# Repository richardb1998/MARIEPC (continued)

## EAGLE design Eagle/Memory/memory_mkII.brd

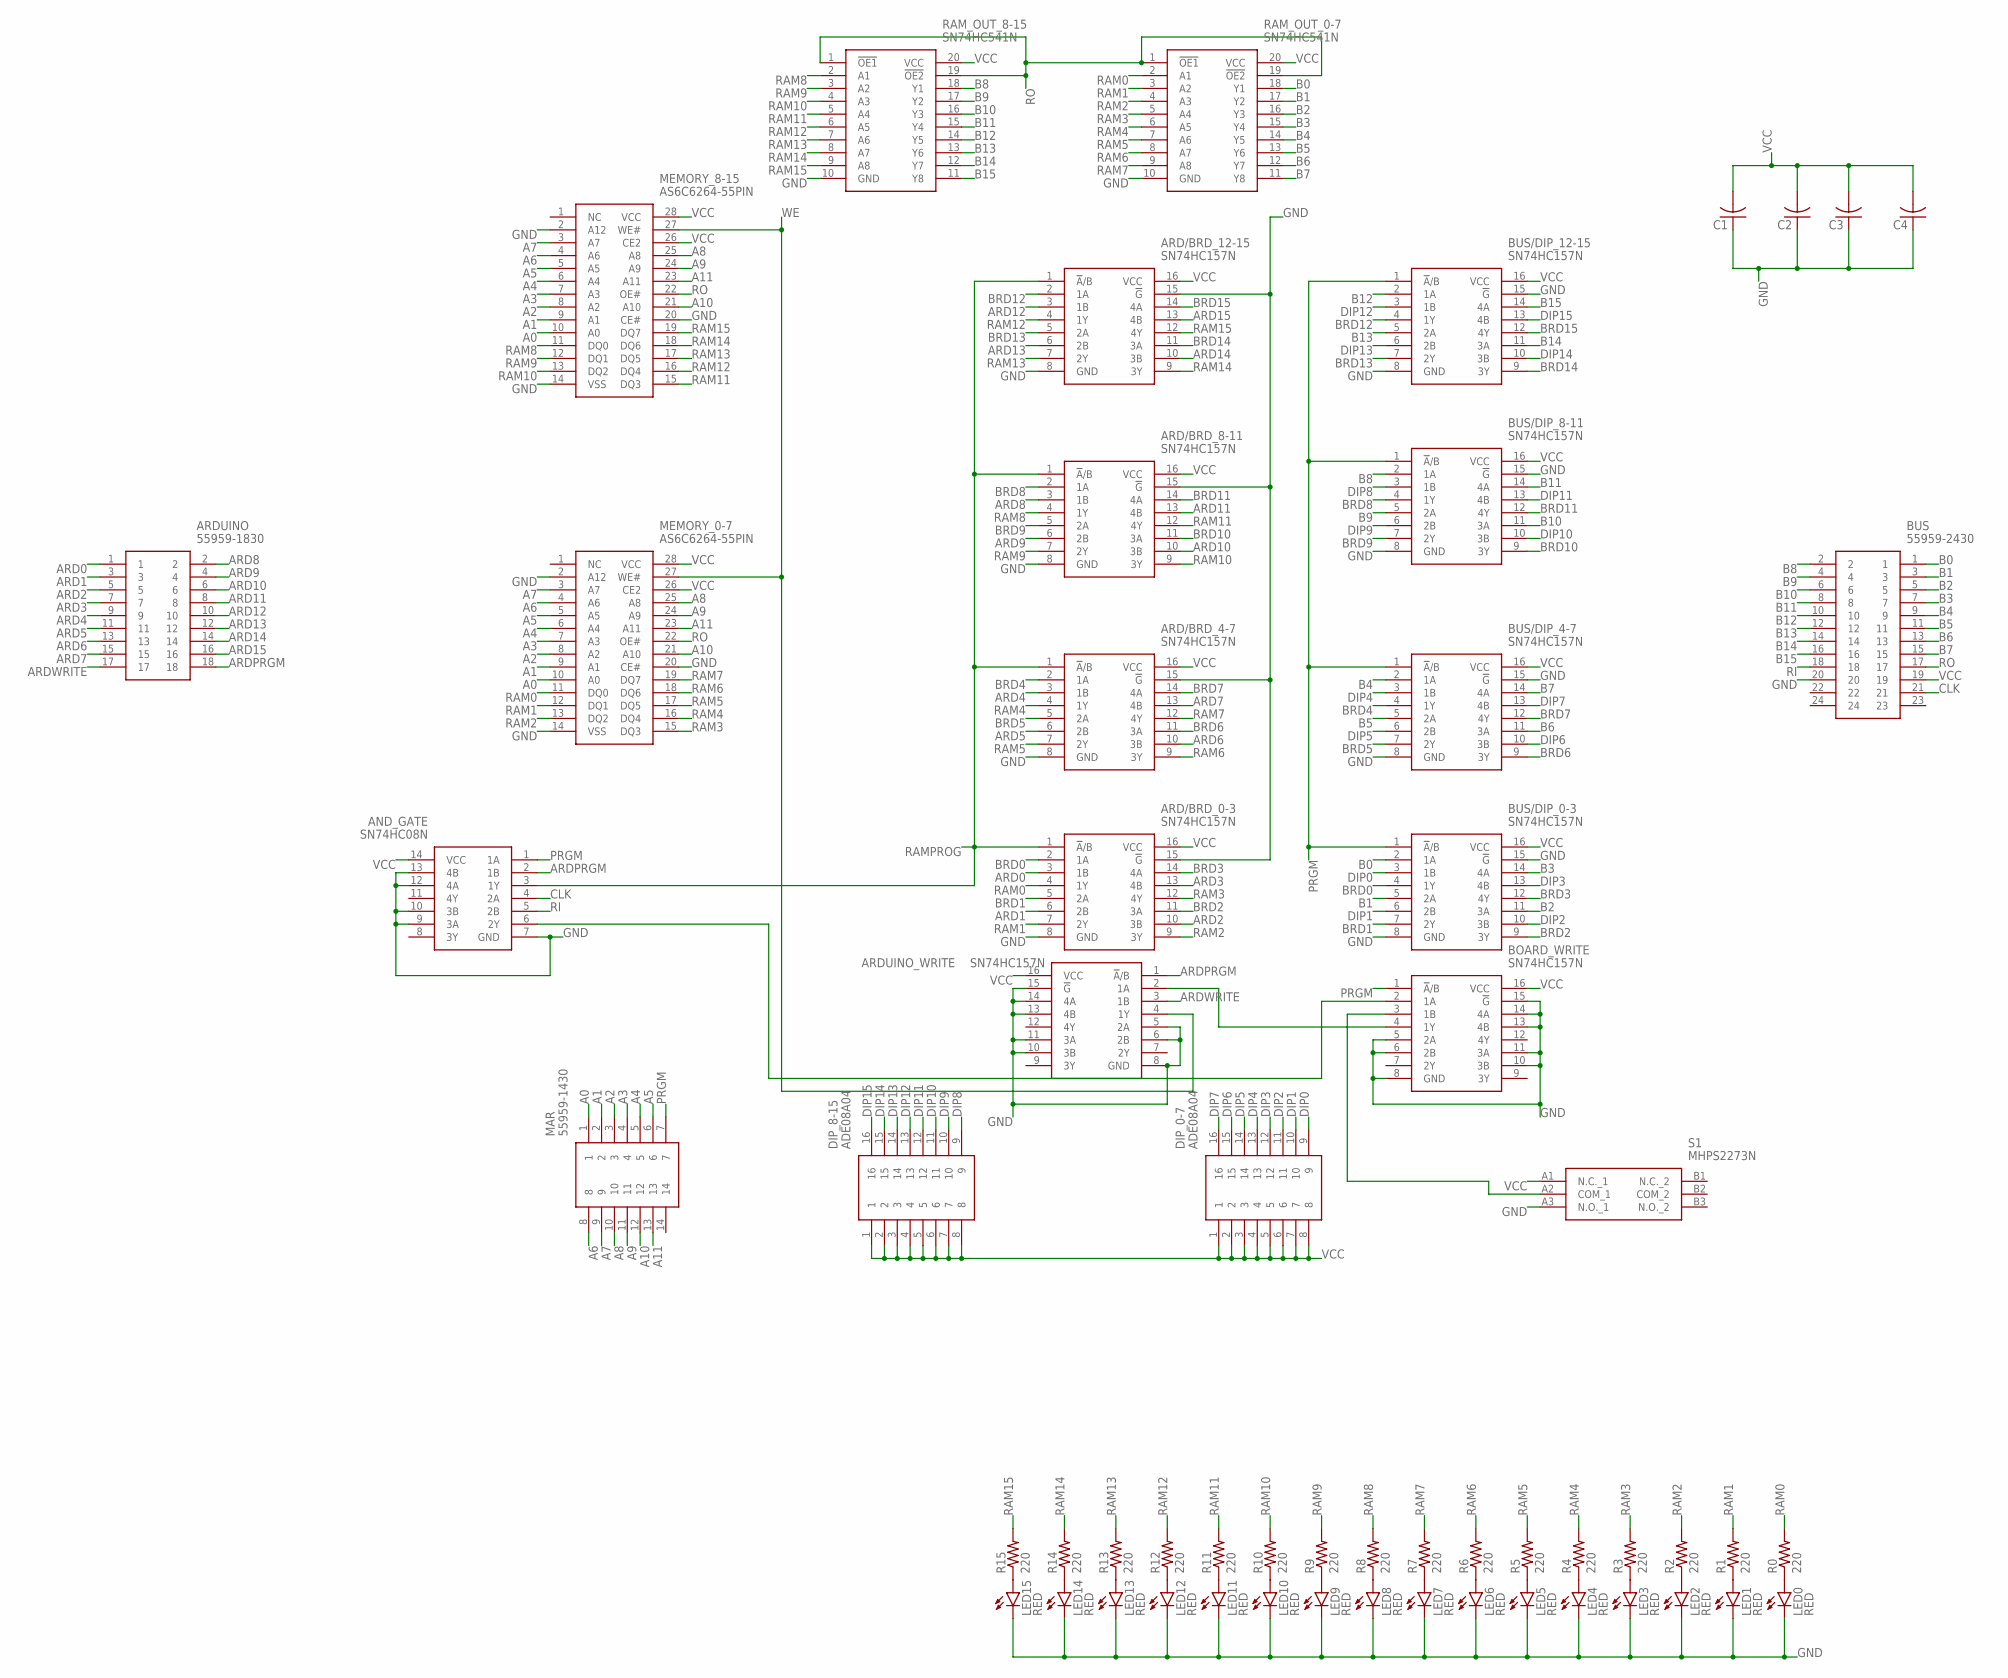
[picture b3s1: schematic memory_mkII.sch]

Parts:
AND_GATE: SN74HC08N; DIP794W53P254L1930H508Q14N
ARD/BRD_0-3, ARD/BRD_4-7, ARD/BRD_8-11, ARD/BRD_12-15: SN74HC157N; DIP794W53P254L1930H508Q16N
ARDUINO: 55959-1830; SHDR18W65P250X200_2X9_2140X140
ARDUINO_WRITE: SN74HC157N; DIP794W53P254L1930H508Q16N
BOARD_WRITE: SN74HC157N; DIP794W53P254L1930H508Q16N
BUS: 55959-2430; 559592430
BUS/DIP_0-3, BUS/DIP_4-7, BUS/DIP_8-11, BUS/DIP_12-15: SN74HC157N; DIP794W53P254L1930H508Q16N
C1, C2, C3, C4: C-US025-024X044; C025-024X044
DIP_0-7, DIP_8-15: ADE08A04; DIP810W60P254L2225H590Q16N
LED0, LED1, LED2, LED3, LED4, LED5, LED6, LED7, LED8, LED9, LED10, LED11, LED12, LED13, LED14, LED15: RED; LED3MM
MAR: 55959-1430; 559591430
MEMORY_0-7, MEMORY_8-15: AS6C6264-55PIN; DIP1524W51P254L3632H394Q28N
R0, R1, R2, R3, R4, R5, R6, R7, R8, R9, R10, R11, R12, R13, R14, R15: 220; 0204/7
RAM_OUT_0-7, RAM_OUT_8-15: SN74HC541N; DIP794W53P254L2540H508Q20N
S1: MHPS2273N

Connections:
A0: MAR.1, MEMORY_0-7.10 (A0), MEMORY_8-15.10 (A0)
A1: MAR.2, MEMORY_0-7.9 (A1), MEMORY_8-15.9 (A1)
A2: MAR.3, MEMORY_0-7.8 (A2), MEMORY_8-15.8 (A2)
A3: MAR.4, MEMORY_0-7.7 (A3), MEMORY_8-15.7 (A3)
A4: MAR.5, MEMORY_0-7.6 (A4), MEMORY_8-15.6 (A4)
A5: MAR.6, MEMORY_0-7.5 (A5), MEMORY_8-15.5 (A5)
A6: MAR.8, MEMORY_0-7.4 (A6), MEMORY_8-15.4 (A6)
A7: MAR.9, MEMORY_0-7.3 (A7), MEMORY_8-15.3 (A7)
A8: MAR.10, MEMORY_0-7.25 (A8), MEMORY_8-15.25 (A8)
A9: MAR.11, MEMORY_0-7.24 (A9), MEMORY_8-15.24 (A9)
A10: MAR.12, MEMORY_0-7.21 (A10), MEMORY_8-15.21 (A10)
A11: MAR.13, MEMORY_0-7.23 (A11), MEMORY_8-15.23 (A11)
ARD0: ARD/BRD_0-3.3 (1B), ARDUINO.1
ARD1: ARD/BRD_0-3.6 (2B), ARDUINO.3
ARD2: ARD/BRD_0-3.10 (3B), ARDUINO.5
ARD3: ARD/BRD_0-3.13 (4B), ARDUINO.7
ARD4: ARD/BRD_4-7.3 (1B), ARDUINO.9
ARD5: ARD/BRD_4-7.6 (2B), ARDUINO.11
ARD6: ARD/BRD_4-7.10 (3B), ARDUINO.13
ARD7: ARD/BRD_4-7.13 (4B), ARDUINO.15
ARD8: ARD/BRD_8-11.3 (1B), ARDUINO.2
ARD9: ARD/BRD_8-11.6 (2B), ARDUINO.4
ARD10: ARD/BRD_8-11.10 (3B), ARDUINO.6
ARD11: ARD/BRD_8-11.13 (4B), ARDUINO.8
ARD12: ARD/BRD_12-15.3 (1B), ARDUINO.10
ARD13: ARD/BRD_12-15.6 (2B), ARDUINO.12
ARD14: ARD/BRD_12-15.10 (3B), ARDUINO.14
ARD15: ARD/BRD_12-15.13 (4B), ARDUINO.16
ARDPRGM: AND_GATE.2 (1B), ARDUINO.18, ARDUINO_WRITE.1 (!A!/B)
ARDWRITE: ARDUINO.17, ARDUINO_WRITE.3 (1B)
B0: BUS.1, BUS/DIP_0-3.2 (1A), RAM_OUT_0-7.18 (Y1)
B1: BUS.3, BUS/DIP_0-3.5 (2A), RAM_OUT_0-7.17 (Y2)
B2: BUS.5, BUS/DIP_0-3.11 (3A), RAM_OUT_0-7.16 (Y3)
B3: BUS.7, BUS/DIP_0-3.14 (4A), RAM_OUT_0-7.15 (Y4)
B4: BUS.9, BUS/DIP_4-7.2 (1A), RAM_OUT_0-7.14 (Y5)
B5: BUS.11, BUS/DIP_4-7.5 (2A), RAM_OUT_0-7.13 (Y6)
B6: BUS.13, BUS/DIP_4-7.11 (3A), RAM_OUT_0-7.12 (Y7)
B7: BUS.15, BUS/DIP_4-7.14 (4A), RAM_OUT_0-7.11 (Y8)
B8: BUS.2, BUS/DIP_8-11.2 (1A), RAM_OUT_8-15.18 (Y1)
B9: BUS.4, BUS/DIP_8-11.5 (2A), RAM_OUT_8-15.17 (Y2)
B10: BUS.6, BUS/DIP_8-11.11 (3A), RAM_OUT_8-15.16 (Y3)
B11: BUS.8, BUS/DIP_8-11.14 (4A), RAM_OUT_8-15.15 (Y4)
B12: BUS.10, BUS/DIP_12-15.2 (1A), RAM_OUT_8-15.14 (Y5)
B13: BUS.12, BUS/DIP_12-15.5 (2A), RAM_OUT_8-15.13 (Y6)
B14: BUS.14, BUS/DIP_12-15.11 (3A), RAM_OUT_8-15.12 (Y7)
B15: BUS.16, BUS/DIP_12-15.14 (4A), RAM_OUT_8-15.11 (Y8)
BRD0: ARD/BRD_0-3.2 (1A), BUS/DIP_0-3.4 (1Y)
BRD1: ARD/BRD_0-3.5 (2A), BUS/DIP_0-3.7 (2Y)
BRD2: ARD/BRD_0-3.11 (3A), BUS/DIP_0-3.9 (3Y)
BRD3: ARD/BRD_0-3.14 (4A), BUS/DIP_0-3.12 (4Y)
BRD4: ARD/BRD_4-7.2 (1A), BUS/DIP_4-7.4 (1Y)
BRD5: ARD/BRD_4-7.5 (2A), BUS/DIP_4-7.7 (2Y)
BRD6: ARD/BRD_4-7.11 (3A), BUS/DIP_4-7.9 (3Y)
BRD7: ARD/BRD_4-7.14 (4A), BUS/DIP_4-7.12 (4Y)
BRD8: ARD/BRD_8-11.2 (1A), BUS/DIP_8-11.4 (1Y)
BRD9: ARD/BRD_8-11.5 (2A), BUS/DIP_8-11.7 (2Y)
BRD10: ARD/BRD_8-11.11 (3A), BUS/DIP_8-11.9 (3Y)
BRD11: ARD/BRD_8-11.14 (4A), BUS/DIP_8-11.12 (4Y)
BRD12: ARD/BRD_12-15.2 (1A), BUS/DIP_12-15.4 (1Y)
BRD13: ARD/BRD_12-15.5 (2A), BUS/DIP_12-15.7 (2Y)
BRD14: ARD/BRD_12-15.11 (3A), BUS/DIP_12-15.9 (3Y)
BRD15: ARD/BRD_12-15.14 (4A), BUS/DIP_12-15.12 (4Y)
CLK: AND_GATE.4 (2A), BUS.21
DIP0: BUS/DIP_0-3.3 (1B), DIP_0-7.9
DIP1: BUS/DIP_0-3.6 (2B), DIP_0-7.10
DIP2: BUS/DIP_0-3.10 (3B), DIP_0-7.11
DIP3: BUS/DIP_0-3.13 (4B), DIP_0-7.12
DIP4: BUS/DIP_4-7.3 (1B), DIP_0-7.13
DIP5: BUS/DIP_4-7.6 (2B), DIP_0-7.14
DIP6: BUS/DIP_4-7.10 (3B), DIP_0-7.15
DIP7: BUS/DIP_4-7.13 (4B), DIP_0-7.16
DIP8: BUS/DIP_8-11.3 (1B), DIP_8-15.9
DIP9: BUS/DIP_8-11.6 (2B), DIP_8-15.10
DIP10: BUS/DIP_8-11.10 (3B), DIP_8-15.11
DIP11: BUS/DIP_8-11.13 (4B), DIP_8-15.12
DIP12: BUS/DIP_12-15.3 (1B), DIP_8-15.13
DIP13: BUS/DIP_12-15.6 (2B), DIP_8-15.14
DIP14: BUS/DIP_12-15.10 (3B), DIP_8-15.15
DIP15: BUS/DIP_12-15.13 (4B), DIP_8-15.16
GND: AND_GATE.7 (GND), AND_GATE.9 (3A), AND_GATE.10 (3B), AND_GATE.12 (4A), AND_GATE.13 (4B), ARD/BRD_0-3.8 (GND), ARD/BRD_0-3.15 (!G), ARD/BRD_4-7.8 (GND), ARD/BRD_4-7.15 (!G), ARD/BRD_8-11.8 (GND), ARD/BRD_8-11.15 (!G), ARD/BRD_12-15.8 (GND), ARD/BRD_12-15.15 (!G), ARDUINO_WRITE.5 (2A), ARDUINO_WRITE.6 (2B), ARDUINO_WRITE.8 (GND), ARDUINO_WRITE.10 (3B), ARDUINO_WRITE.11 (3A), ARDUINO_WRITE.13 (4B), ARDUINO_WRITE.14 (4A), ARDUINO_WRITE.15 (!G), BOARD_WRITE.5 (2A), BOARD_WRITE.6 (2B), BOARD_WRITE.8 (GND), BOARD_WRITE.10 (3B), BOARD_WRITE.11 (3A), BOARD_WRITE.13 (4B), BOARD_WRITE.14 (4A), BOARD_WRITE.15 (!G), BUS.20, BUS/DIP_0-3.8 (GND), BUS/DIP_0-3.15 (!G), BUS/DIP_4-7.8 (GND), BUS/DIP_4-7.15 (!G), BUS/DIP_8-11.8 (GND), BUS/DIP_8-11.15 (!G), BUS/DIP_12-15.8 (GND), BUS/DIP_12-15.15 (!G), C1.1, C2.1, C3.1, C4.1, LED0.K (C), LED1.K (C), LED2.K (C), LED3.K (C), LED4.K (C), LED5.K (C), LED6.K (C), LED7.K (C), LED8.K (C), LED9.K (C), LED10.K (C), LED11.K (C), LED12.K (C), LED13.K (C), LED14.K (C), LED15.K (C), MEMORY_0-7.2 (A12), MEMORY_0-7.14 (VSS), MEMORY_0-7.20 (CE#), MEMORY_8-15.2 (A12), MEMORY_8-15.14 (VSS), MEMORY_8-15.20 (CE#), RAM_OUT_0-7.10 (GND), RAM_OUT_8-15.10 (GND), S1.A3 (N.O._1)
unnamed: LED1.A, R1.1
unnamed: BOARD_WRITE.3 (1B), S1.A2 (COM_1)
unnamed: ARDUINO_WRITE.2 (1A), BOARD_WRITE.4 (1Y)
unnamed: LED2.A, R2.1
unnamed: LED3.A, R3.1
unnamed: LED4.A, R4.1
unnamed: LED5.A, R5.1
unnamed: LED6.A, R6.1
unnamed: LED7.A, R7.1
unnamed: LED8.A, R8.1
unnamed: LED9.A, R9.1
unnamed: LED10.A, R10.1
unnamed: LED11.A, R11.1
unnamed: LED12.A, R12.1
unnamed: LED13.A, R13.1
unnamed: LED14.A, R14.1
unnamed: LED15.A, R15.1
unnamed: LED0.A, R0.1
PRGM: AND_GATE.1 (1A), BOARD_WRITE.1 (!A!/B), BUS/DIP_0-3.1 (!A!/B), BUS/DIP_4-7.1 (!A!/B), BUS/DIP_8-11.1 (!A!/B), BUS/DIP_12-15.1 (!A!/B), MAR.7
RAM0: ARD/BRD_0-3.4 (1Y), MEMORY_0-7.11 (DQ0), R0.2, RAM_OUT_0-7.2 (A1)
RAM1: ARD/BRD_0-3.7 (2Y), MEMORY_0-7.12 (DQ1), R1.2, RAM_OUT_0-7.3 (A2)
RAM2: ARD/BRD_0-3.9 (3Y), MEMORY_0-7.13 (DQ2), R2.2, RAM_OUT_0-7.4 (A3)
RAM3: ARD/BRD_0-3.12 (4Y), MEMORY_0-7.15 (DQ3), R3.2, RAM_OUT_0-7.5 (A4)
RAM4: ARD/BRD_4-7.4 (1Y), MEMORY_0-7.16 (DQ4), R4.2, RAM_OUT_0-7.6 (A5)
RAM5: ARD/BRD_4-7.7 (2Y), MEMORY_0-7.17 (DQ5), R5.2, RAM_OUT_0-7.7 (A6)
RAM6: ARD/BRD_4-7.9 (3Y), MEMORY_0-7.18 (DQ6), R6.2, RAM_OUT_0-7.8 (A7)
RAM7: ARD/BRD_4-7.12 (4Y), MEMORY_0-7.19 (DQ7), R7.2, RAM_OUT_0-7.9 (A8)
RAM8: ARD/BRD_8-11.4 (1Y), MEMORY_8-15.11 (DQ0), R8.2, RAM_OUT_8-15.2 (A1)
RAM9: ARD/BRD_8-11.7 (2Y), MEMORY_8-15.12 (DQ1), R9.2, RAM_OUT_8-15.3 (A2)
RAM10: ARD/BRD_8-11.9 (3Y), MEMORY_8-15.13 (DQ2), R10.2, RAM_OUT_8-15.4 (A3)
RAM11: ARD/BRD_8-11.12 (4Y), MEMORY_8-15.15 (DQ3), R11.2, RAM_OUT_8-15.5 (A4)
RAM12: ARD/BRD_12-15.4 (1Y), MEMORY_8-15.16 (DQ4), R12.2, RAM_OUT_8-15.6 (A5)
RAM13: ARD/BRD_12-15.7 (2Y), MEMORY_8-15.17 (DQ5), R13.2, RAM_OUT_8-15.7 (A6)
RAM14: ARD/BRD_12-15.9 (3Y), MEMORY_8-15.18 (DQ6), R14.2, RAM_OUT_8-15.8 (A7)
RAM15: ARD/BRD_12-15.12 (4Y), MEMORY_8-15.19 (DQ7), R15.2, RAM_OUT_8-15.9 (A8)
RAMCLK: AND_GATE.6 (2Y), BOARD_WRITE.2 (1A)
RAMPROG: AND_GATE.3 (1Y), ARD/BRD_0-3.1 (!A!/B), ARD/BRD_4-7.1 (!A!/B), ARD/BRD_8-11.1 (!A!/B), ARD/BRD_12-15.1 (!A!/B)
RI: AND_GATE.5 (2B), BUS.18
RO: BUS.17, MEMORY_0-7.22 (OE#), MEMORY_8-15.22 (OE#), RAM_OUT_0-7.1 (!OE1), RAM_OUT_0-7.19 (!OE2), RAM_OUT_8-15.1 (!OE1), RAM_OUT_8-15.19 (!OE2)
VCC: AND_GATE.14 (VCC), ARD/BRD_0-3.16 (VCC), ARD/BRD_4-7.16 (VCC), ARD/BRD_8-11.16 (VCC), ARD/BRD_12-15.16 (VCC), ARDUINO_WRITE.16 (VCC), BOARD_WRITE.16 (VCC), BUS.19, BUS/DIP_0-3.16 (VCC), BUS/DIP_4-7.16 (VCC), BUS/DIP_8-11.16 (VCC), BUS/DIP_12-15.16 (VCC), C1.2, C2.2, C3.2, C4.2, DIP_0-7.1, DIP_0-7.2, DIP_0-7.3, DIP_0-7.4, DIP_0-7.5, DIP_0-7.6, DIP_0-7.7, DIP_0-7.8, DIP_8-15.1, DIP_8-15.2, DIP_8-15.3, DIP_8-15.4, DIP_8-15.5, DIP_8-15.6, DIP_8-15.7, DIP_8-15.8, MEMORY_0-7.26 (CE2), MEMORY_0-7.28 (VCC), MEMORY_8-15.26 (CE2), MEMORY_8-15.28 (VCC), RAM_OUT_0-7.20 (VCC), RAM_OUT_8-15.20 (VCC), S1.A1 (N.C._1)
WE: ARDUINO_WRITE.4 (1Y), MEMORY_0-7.27 (WE#), MEMORY_8-15.27 (WE#)

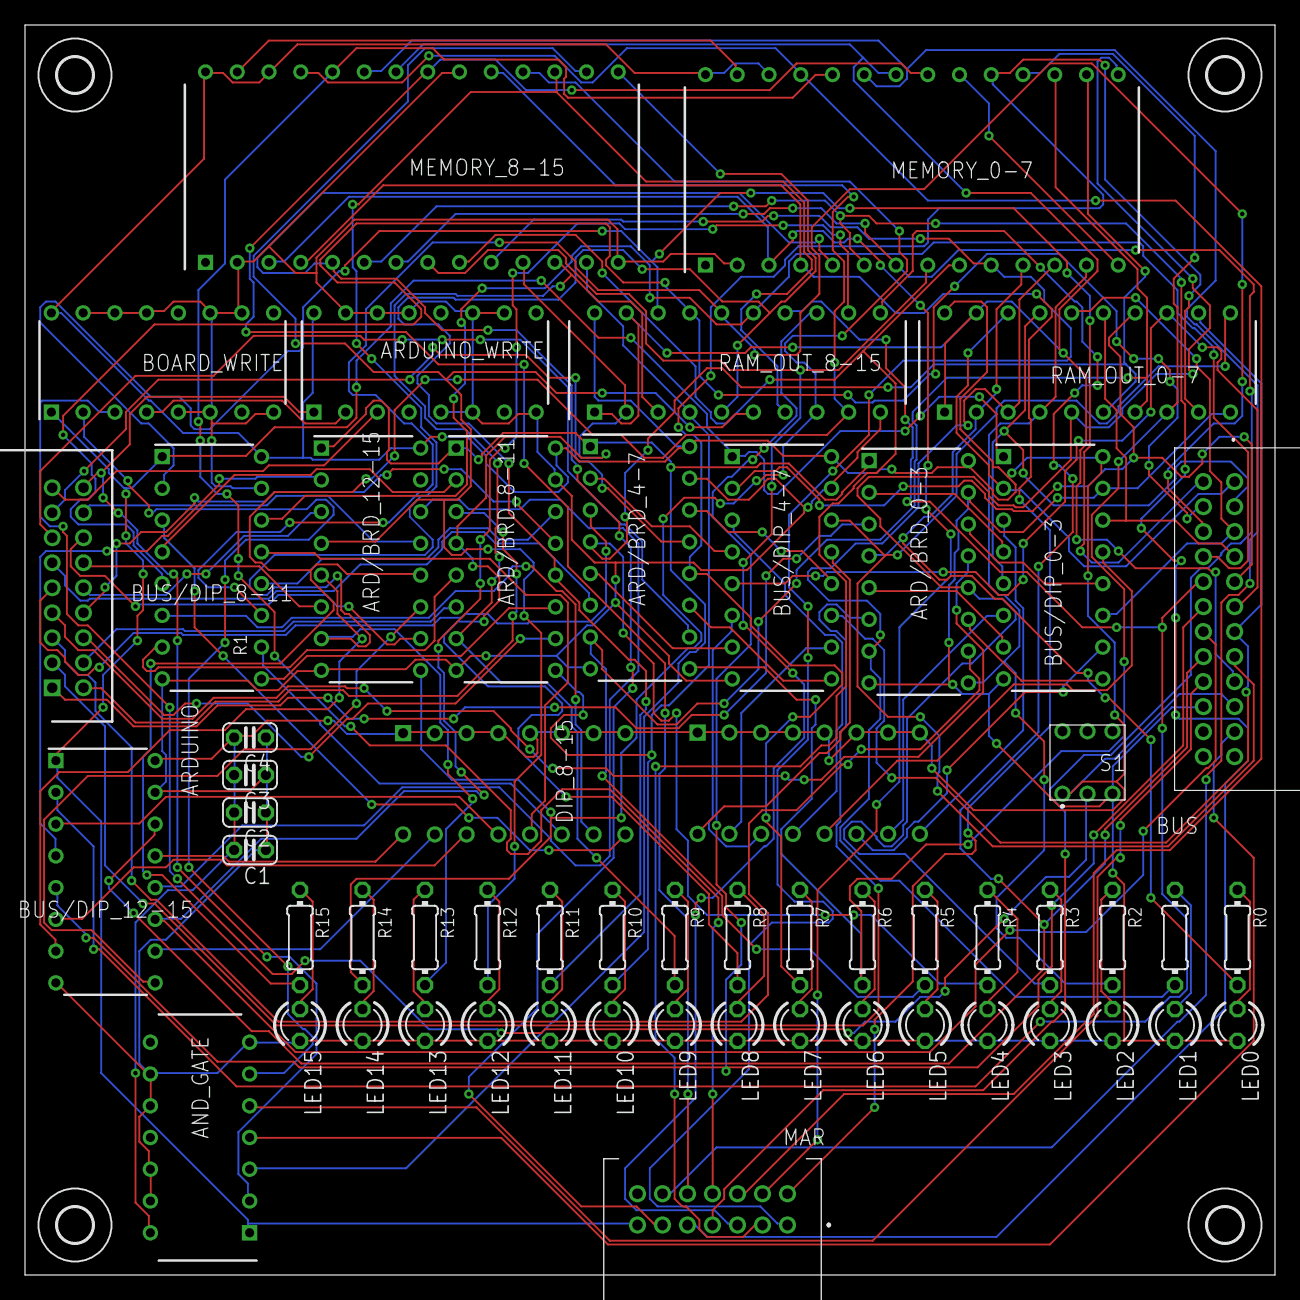
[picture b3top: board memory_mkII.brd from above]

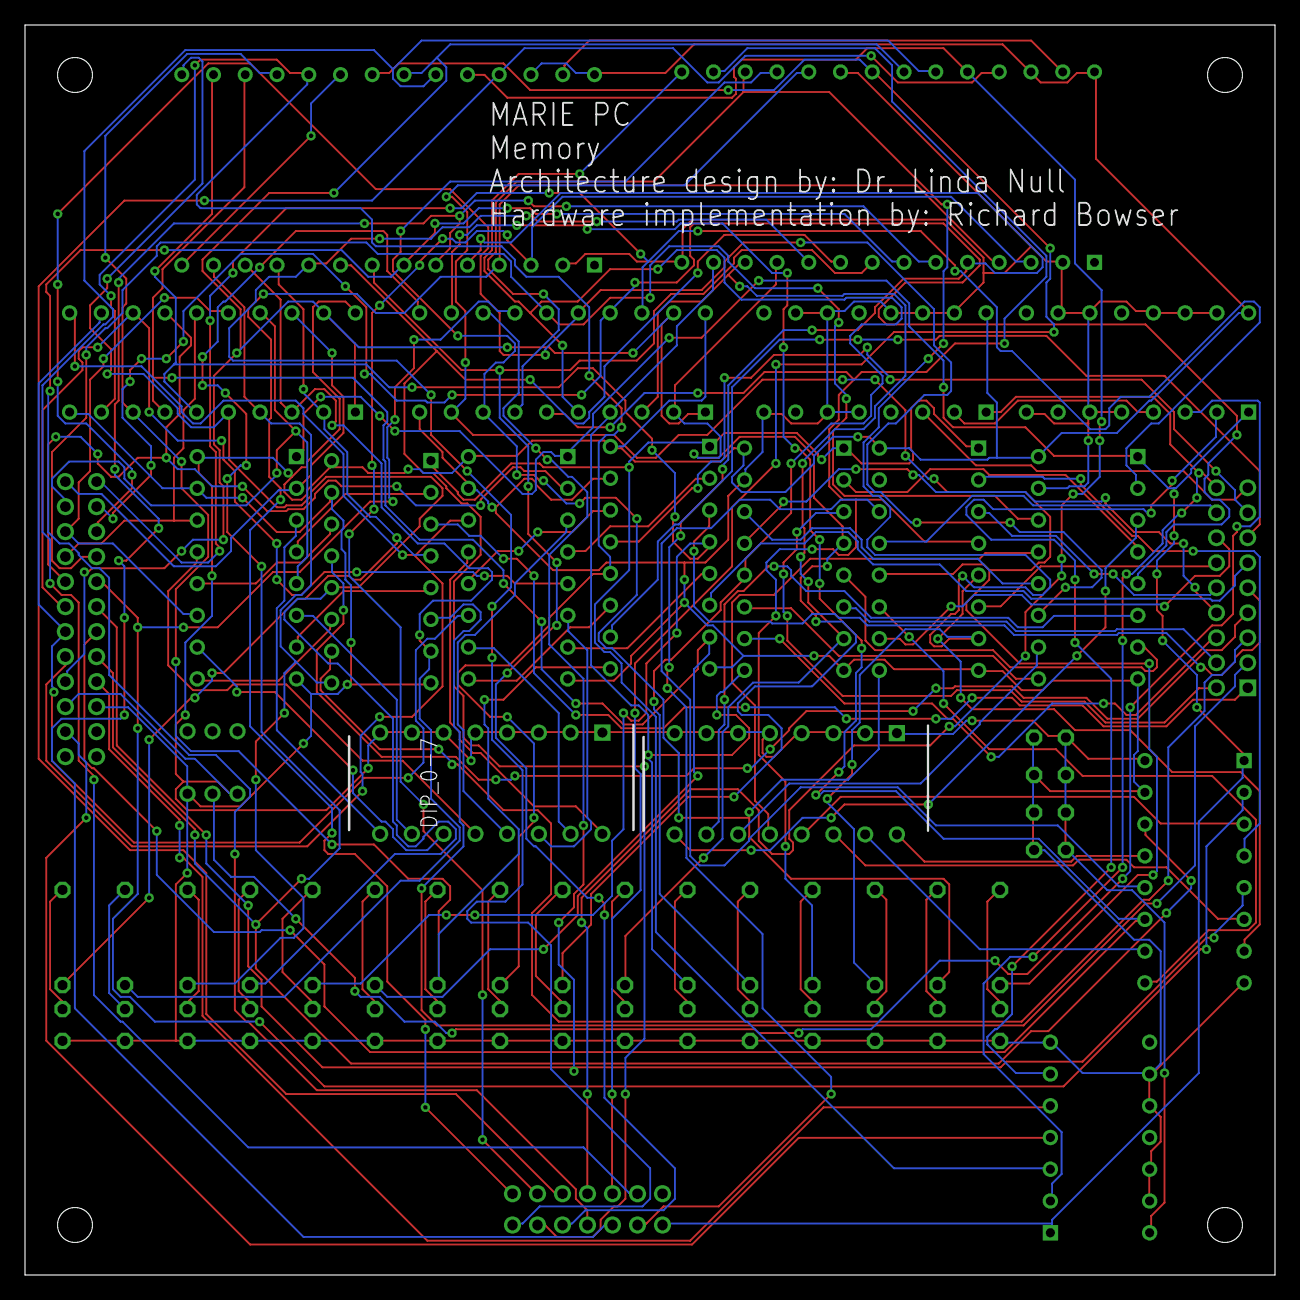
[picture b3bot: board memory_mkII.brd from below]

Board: 2 copper layers, 100.0 x 100.0 mm, 61 parts (2 on the bottom side), 121 nets.

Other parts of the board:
U$1, U$2, U$3, U$4: 2,8

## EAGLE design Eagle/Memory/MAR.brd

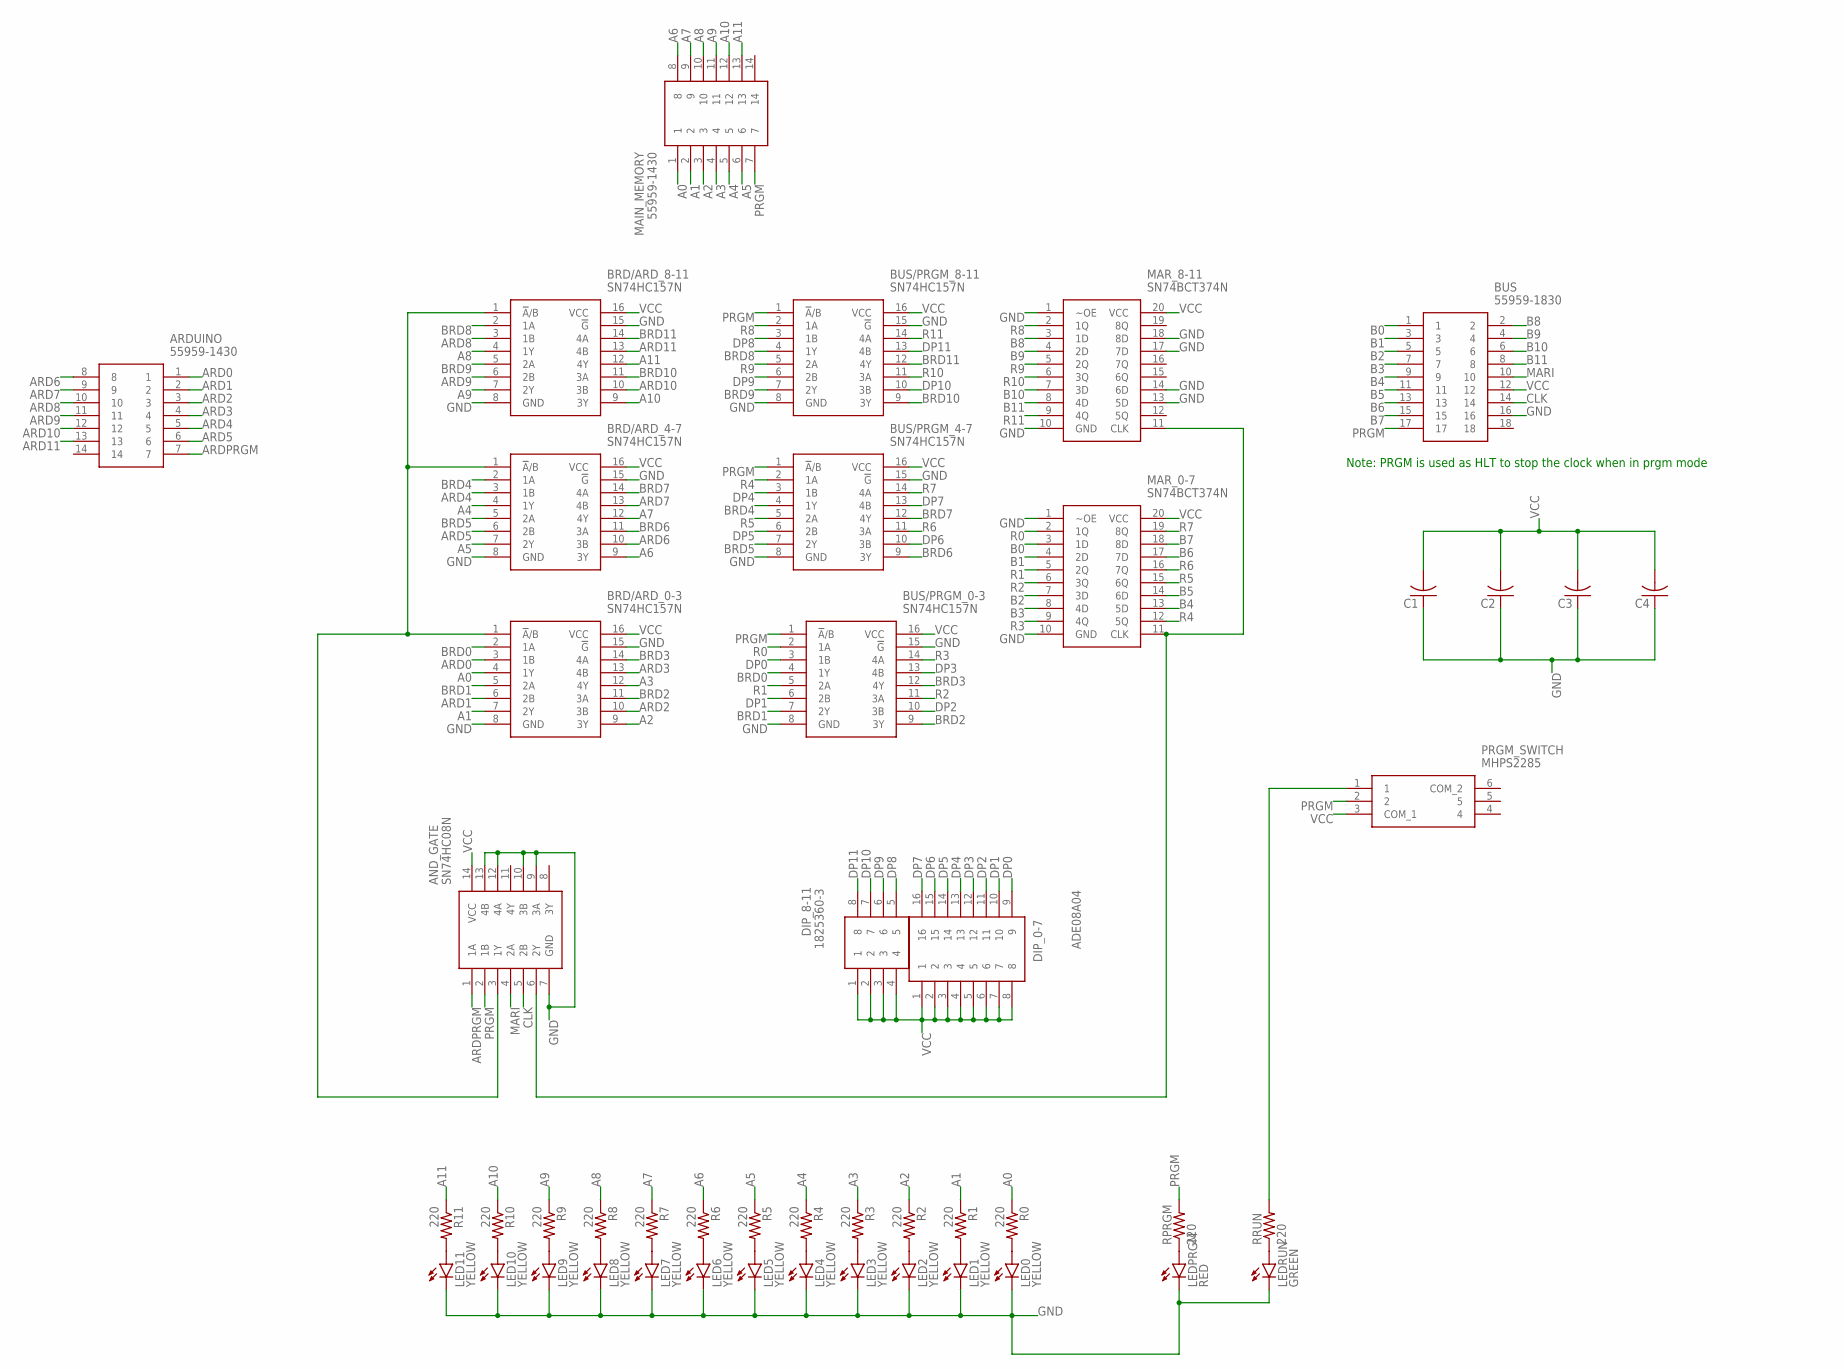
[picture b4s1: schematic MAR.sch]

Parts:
AND_GATE: SN74HC08N; DIP794W53P254L1930H508Q14N
ARDUINO: 55959-1430; 559591430
BRD/ARD_0-3, BRD/ARD_4-7, BRD/ARD_8-11: SN74HC157N; DIP794W53P254L1930H508Q16N
BUS: 55959-1830; SHDR18W65P250X200_2X9_2140X140
BUS/PRGM_0-3, BUS/PRGM_4-7, BUS/PRGM_8-11: SN74HC157N; DIP794W53P254L1930H508Q16N
C1, C2, C3, C4: C-US025-024X044; C025-024X044
DIP_0-7: ADE08A04; DIP810W60P254L2225H590Q16N
DIP_8-11: 1825360-3; DIP813W61P254L1209H351Q8N
LED0, LED1, LED2, LED3, LED4, LED5, LED6, LED7, LED8, LED9, LED10, LED11: YELLOW; LED3MM
LEDPRGM: RED; LED3MM
LEDRUN: GREEN; LED3MM
MAIN_MEMORY: 55959-1430; 559591430
MAR_0-7, MAR_8-11: SN74BCT374N; DIP254P762X508-20
PRGM_SWITCH: MHPS2285
R0, R1, R2, R3, R4, R5, R6, R7, R8, R9, R10, R11: 220; 0204/7
RPRGM: 220; 0204/7
RRUN: 220; 0204/7

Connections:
A0: BRD/ARD_0-3.4 (1Y), MAIN_MEMORY.1, R0.1
A1: BRD/ARD_0-3.7 (2Y), MAIN_MEMORY.2, R1.1
A2: BRD/ARD_0-3.9 (3Y), MAIN_MEMORY.3, R2.1
A3: BRD/ARD_0-3.12 (4Y), MAIN_MEMORY.4, R3.1
A4: BRD/ARD_4-7.4 (1Y), MAIN_MEMORY.5, R4.1
A5: BRD/ARD_4-7.7 (2Y), MAIN_MEMORY.6, R5.1
A6: BRD/ARD_4-7.9 (3Y), MAIN_MEMORY.8, R6.1
A7: BRD/ARD_4-7.12 (4Y), MAIN_MEMORY.9, R7.1
A8: BRD/ARD_8-11.4 (1Y), MAIN_MEMORY.10, R8.1
A9: BRD/ARD_8-11.7 (2Y), MAIN_MEMORY.11, R9.1
A10: BRD/ARD_8-11.9 (3Y), MAIN_MEMORY.12, R10.1
A11: BRD/ARD_8-11.12 (4Y), MAIN_MEMORY.13, R11.1
ARD0: ARDUINO.1, BRD/ARD_0-3.3 (1B)
ARD1: ARDUINO.2, BRD/ARD_0-3.6 (2B)
ARD2: ARDUINO.3, BRD/ARD_0-3.10 (3B)
ARD3: ARDUINO.4, BRD/ARD_0-3.13 (4B)
ARD4: ARDUINO.5, BRD/ARD_4-7.3 (1B)
ARD5: ARDUINO.6, BRD/ARD_4-7.6 (2B)
ARD6: ARDUINO.8, BRD/ARD_4-7.10 (3B)
ARD7: ARDUINO.9, BRD/ARD_4-7.13 (4B)
ARD8: ARDUINO.10, BRD/ARD_8-11.3 (1B)
ARD9: ARDUINO.11, BRD/ARD_8-11.6 (2B)
ARD10: ARDUINO.12, BRD/ARD_8-11.10 (3B)
ARD11: ARDUINO.13, BRD/ARD_8-11.13 (4B)
ARDPRGM: AND_GATE.1 (1A), ARDUINO.7
B0: BUS.1, MAR_0-7.3 (1D)
B1: BUS.3, MAR_0-7.4 (2D)
B2: BUS.5, MAR_0-7.7 (3D)
B3: BUS.7, MAR_0-7.8 (4D)
B4: BUS.9, MAR_0-7.13 (5D)
B5: BUS.11, MAR_0-7.14 (6D)
B6: BUS.13, MAR_0-7.17 (7D)
B7: BUS.15, MAR_0-7.18 (8D)
B8: BUS.2, MAR_8-11.3 (1D)
B9: BUS.4, MAR_8-11.4 (2D)
B10: BUS.6, MAR_8-11.7 (3D)
B11: BUS.8, MAR_8-11.8 (4D)
BRD0: BRD/ARD_0-3.2 (1A), BUS/PRGM_0-3.4 (1Y)
BRD1: BRD/ARD_0-3.5 (2A), BUS/PRGM_0-3.7 (2Y)
BRD2: BRD/ARD_0-3.11 (3A), BUS/PRGM_0-3.9 (3Y)
BRD3: BRD/ARD_0-3.14 (4A), BUS/PRGM_0-3.12 (4Y)
BRD4: BRD/ARD_4-7.2 (1A), BUS/PRGM_4-7.4 (1Y)
BRD5: BRD/ARD_4-7.5 (2A), BUS/PRGM_4-7.7 (2Y)
BRD6: BRD/ARD_4-7.11 (3A), BUS/PRGM_4-7.9 (3Y)
BRD7: BRD/ARD_4-7.14 (4A), BUS/PRGM_4-7.12 (4Y)
BRD8: BRD/ARD_8-11.2 (1A), BUS/PRGM_8-11.4 (1Y)
BRD9: BRD/ARD_8-11.5 (2A), BUS/PRGM_8-11.7 (2Y)
BRD10: BRD/ARD_8-11.11 (3A), BUS/PRGM_8-11.9 (3Y)
BRD11: BRD/ARD_8-11.14 (4A), BUS/PRGM_8-11.12 (4Y)
CLK: AND_GATE.5 (2B), BUS.14
DP0: BUS/PRGM_0-3.3 (1B), DIP_0-7.9
DP1: BUS/PRGM_0-3.6 (2B), DIP_0-7.10
DP2: BUS/PRGM_0-3.10 (3B), DIP_0-7.11
DP3: BUS/PRGM_0-3.13 (4B), DIP_0-7.12
DP4: BUS/PRGM_4-7.3 (1B), DIP_0-7.13
DP5: BUS/PRGM_4-7.6 (2B), DIP_0-7.14
DP6: BUS/PRGM_4-7.10 (3B), DIP_0-7.15
DP7: BUS/PRGM_4-7.13 (4B), DIP_0-7.16
DP8: BUS/PRGM_8-11.3 (1B), DIP_8-11.5
DP9: BUS/PRGM_8-11.6 (2B), DIP_8-11.6
DP10: BUS/PRGM_8-11.10 (3B), DIP_8-11.7
DP11: BUS/PRGM_8-11.13 (4B), DIP_8-11.8
GND: AND_GATE.7 (GND), AND_GATE.9 (3A), AND_GATE.10 (3B), AND_GATE.12 (4A), AND_GATE.13 (4B), BRD/ARD_0-3.8 (GND), BRD/ARD_0-3.15 (!G), BRD/ARD_4-7.8 (GND), BRD/ARD_4-7.15 (!G), BRD/ARD_8-11.8 (GND), BRD/ARD_8-11.15 (!G), BUS.16, BUS/PRGM_0-3.8 (GND), BUS/PRGM_0-3.15 (!G), BUS/PRGM_4-7.8 (GND), BUS/PRGM_4-7.15 (!G), BUS/PRGM_8-11.8 (GND), BUS/PRGM_8-11.15 (!G), C1.1, C2.1, C3.1, C4.1, LED0.K (C), LED1.K (C), LED2.K (C), LED3.K (C), LED4.K (C), LED5.K (C), LED6.K (C), LED7.K (C), LED8.K (C), LED9.K (C), LED10.K (C), LED11.K (C), LEDPRGM.K (C), LEDRUN.K (C), MAR_0-7.1 (~OE), MAR_0-7.10 (GND), MAR_8-11.1 (~OE), MAR_8-11.10 (GND), MAR_8-11.13 (5D), MAR_8-11.14 (6D), MAR_8-11.17 (7D), MAR_8-11.18 (8D)
MARI: AND_GATE.4 (2A), BUS.10
unnamed: AND_GATE.3 (1Y), BRD/ARD_0-3.1 (!A!/B), BRD/ARD_4-7.1 (!A!/B), BRD/ARD_8-11.1 (!A!/B)
unnamed: AND_GATE.6 (2Y), MAR_0-7.11 (CLK), MAR_8-11.11 (CLK)
unnamed: LED1.A, R1.2
unnamed: LED2.A, R2.2
unnamed: LED3.A, R3.2
unnamed: LED4.A, R4.2
unnamed: LED5.A, R5.2
unnamed: LED6.A, R6.2
unnamed: LED7.A, R7.2
unnamed: LED8.A, R8.2
unnamed: LEDPRGM.A, RPRGM.1
unnamed: LEDRUN.A, RRUN.1
unnamed: PRGM_SWITCH.1, RRUN.2
unnamed: LED9.A, R9.2
unnamed: LED10.A, R10.2
unnamed: LED11.A, R11.2
unnamed: LED0.A, R0.2
PRGM: AND_GATE.2 (1B), BUS.17, BUS/PRGM_0-3.1 (!A!/B), BUS/PRGM_4-7.1 (!A!/B), BUS/PRGM_8-11.1 (!A!/B), MAIN_MEMORY.7, PRGM_SWITCH.2, RPRGM.2
R0: BUS/PRGM_0-3.2 (1A), MAR_0-7.2 (1Q)
R1: BUS/PRGM_0-3.5 (2A), MAR_0-7.5 (2Q)
R2: BUS/PRGM_0-3.11 (3A), MAR_0-7.6 (3Q)
R3: BUS/PRGM_0-3.14 (4A), MAR_0-7.9 (4Q)
R4: BUS/PRGM_4-7.2 (1A), MAR_0-7.12 (5Q)
R5: BUS/PRGM_4-7.5 (2A), MAR_0-7.15 (6Q)
R6: BUS/PRGM_4-7.11 (3A), MAR_0-7.16 (7Q)
R7: BUS/PRGM_4-7.14 (4A), MAR_0-7.19 (8Q)
R8: BUS/PRGM_8-11.2 (1A), MAR_8-11.2 (1Q)
R9: BUS/PRGM_8-11.5 (2A), MAR_8-11.5 (2Q)
R10: BUS/PRGM_8-11.11 (3A), MAR_8-11.6 (3Q)
R11: BUS/PRGM_8-11.14 (4A), MAR_8-11.9 (4Q)
VCC: AND_GATE.14 (VCC), BRD/ARD_0-3.16 (VCC), BRD/ARD_4-7.16 (VCC), BRD/ARD_8-11.16 (VCC), BUS.12, BUS/PRGM_0-3.16 (VCC), BUS/PRGM_4-7.16 (VCC), BUS/PRGM_8-11.16 (VCC), C1.2, C2.2, C3.2, C4.2, DIP_0-7.1, DIP_0-7.2, DIP_0-7.3, DIP_0-7.4, DIP_0-7.5, DIP_0-7.6, DIP_0-7.7, DIP_0-7.8, DIP_8-11.1, DIP_8-11.2, DIP_8-11.3, DIP_8-11.4, MAR_0-7.20 (VCC), MAR_8-11.20 (VCC), PRGM_SWITCH.3 (COM_1)

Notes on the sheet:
Note: PRGM is used as HLT to stop the clock when in prgm mode

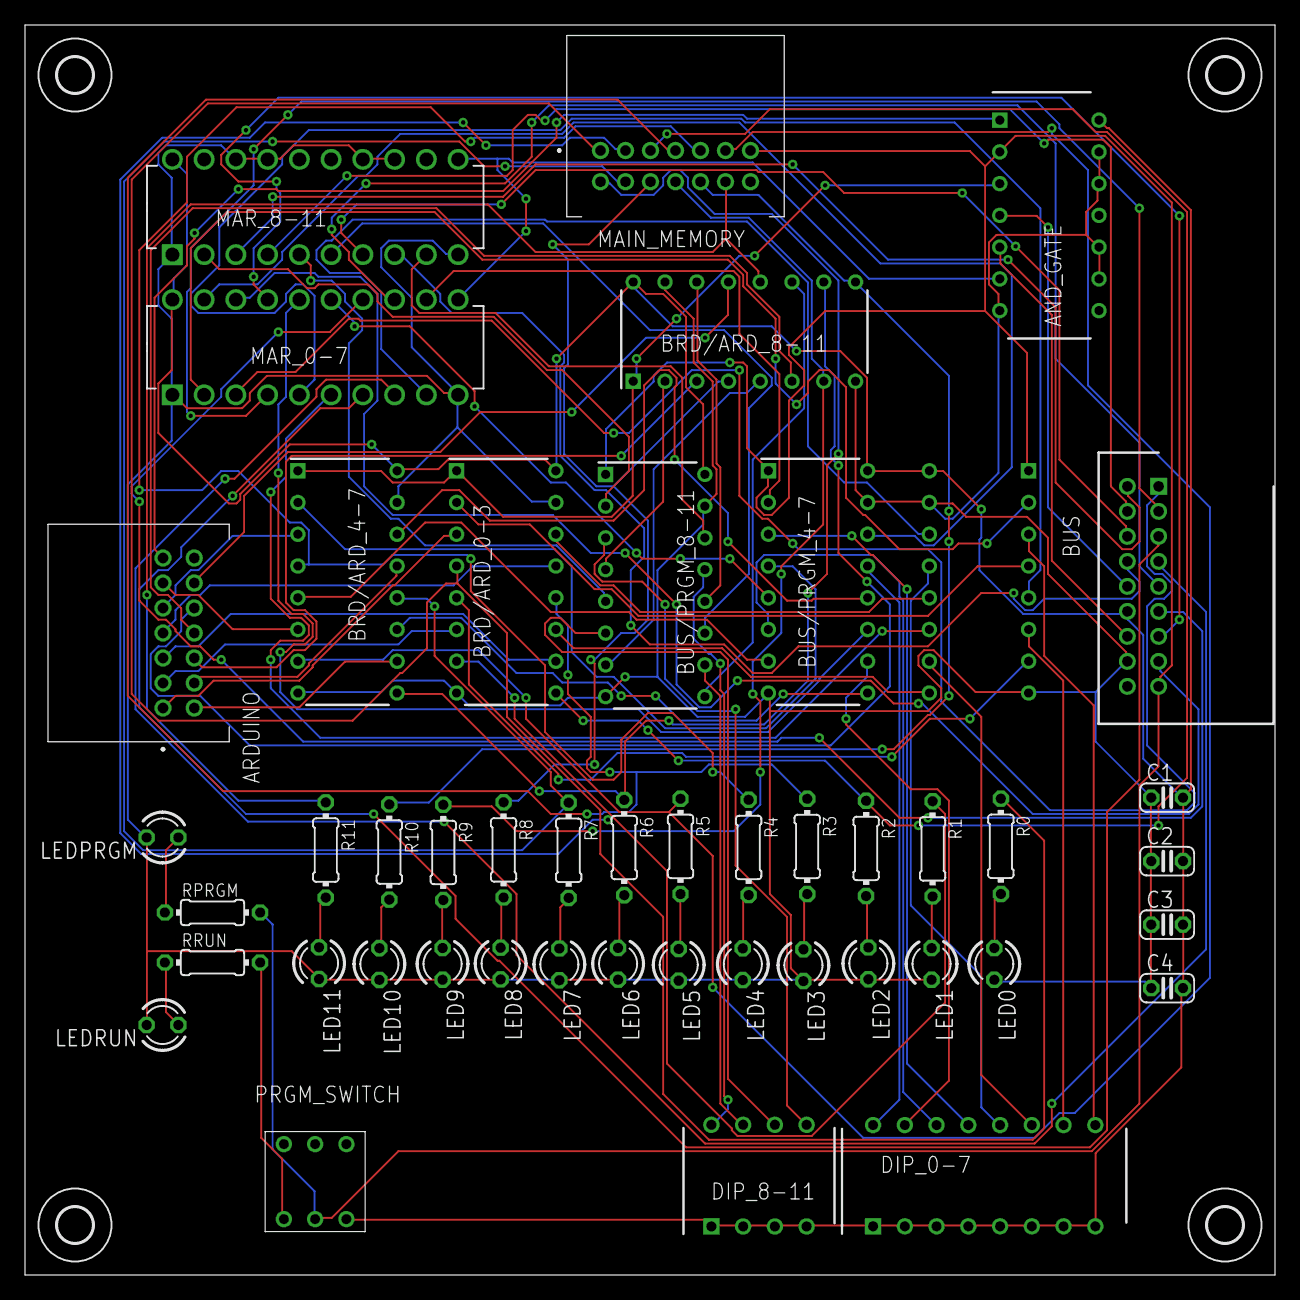
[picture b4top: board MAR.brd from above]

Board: 2 copper layers, 100.0 x 100.0 mm, 51 parts (1 on the bottom side), 95 nets.

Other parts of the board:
U$1, U$2, U$3, U$4: 2,8
